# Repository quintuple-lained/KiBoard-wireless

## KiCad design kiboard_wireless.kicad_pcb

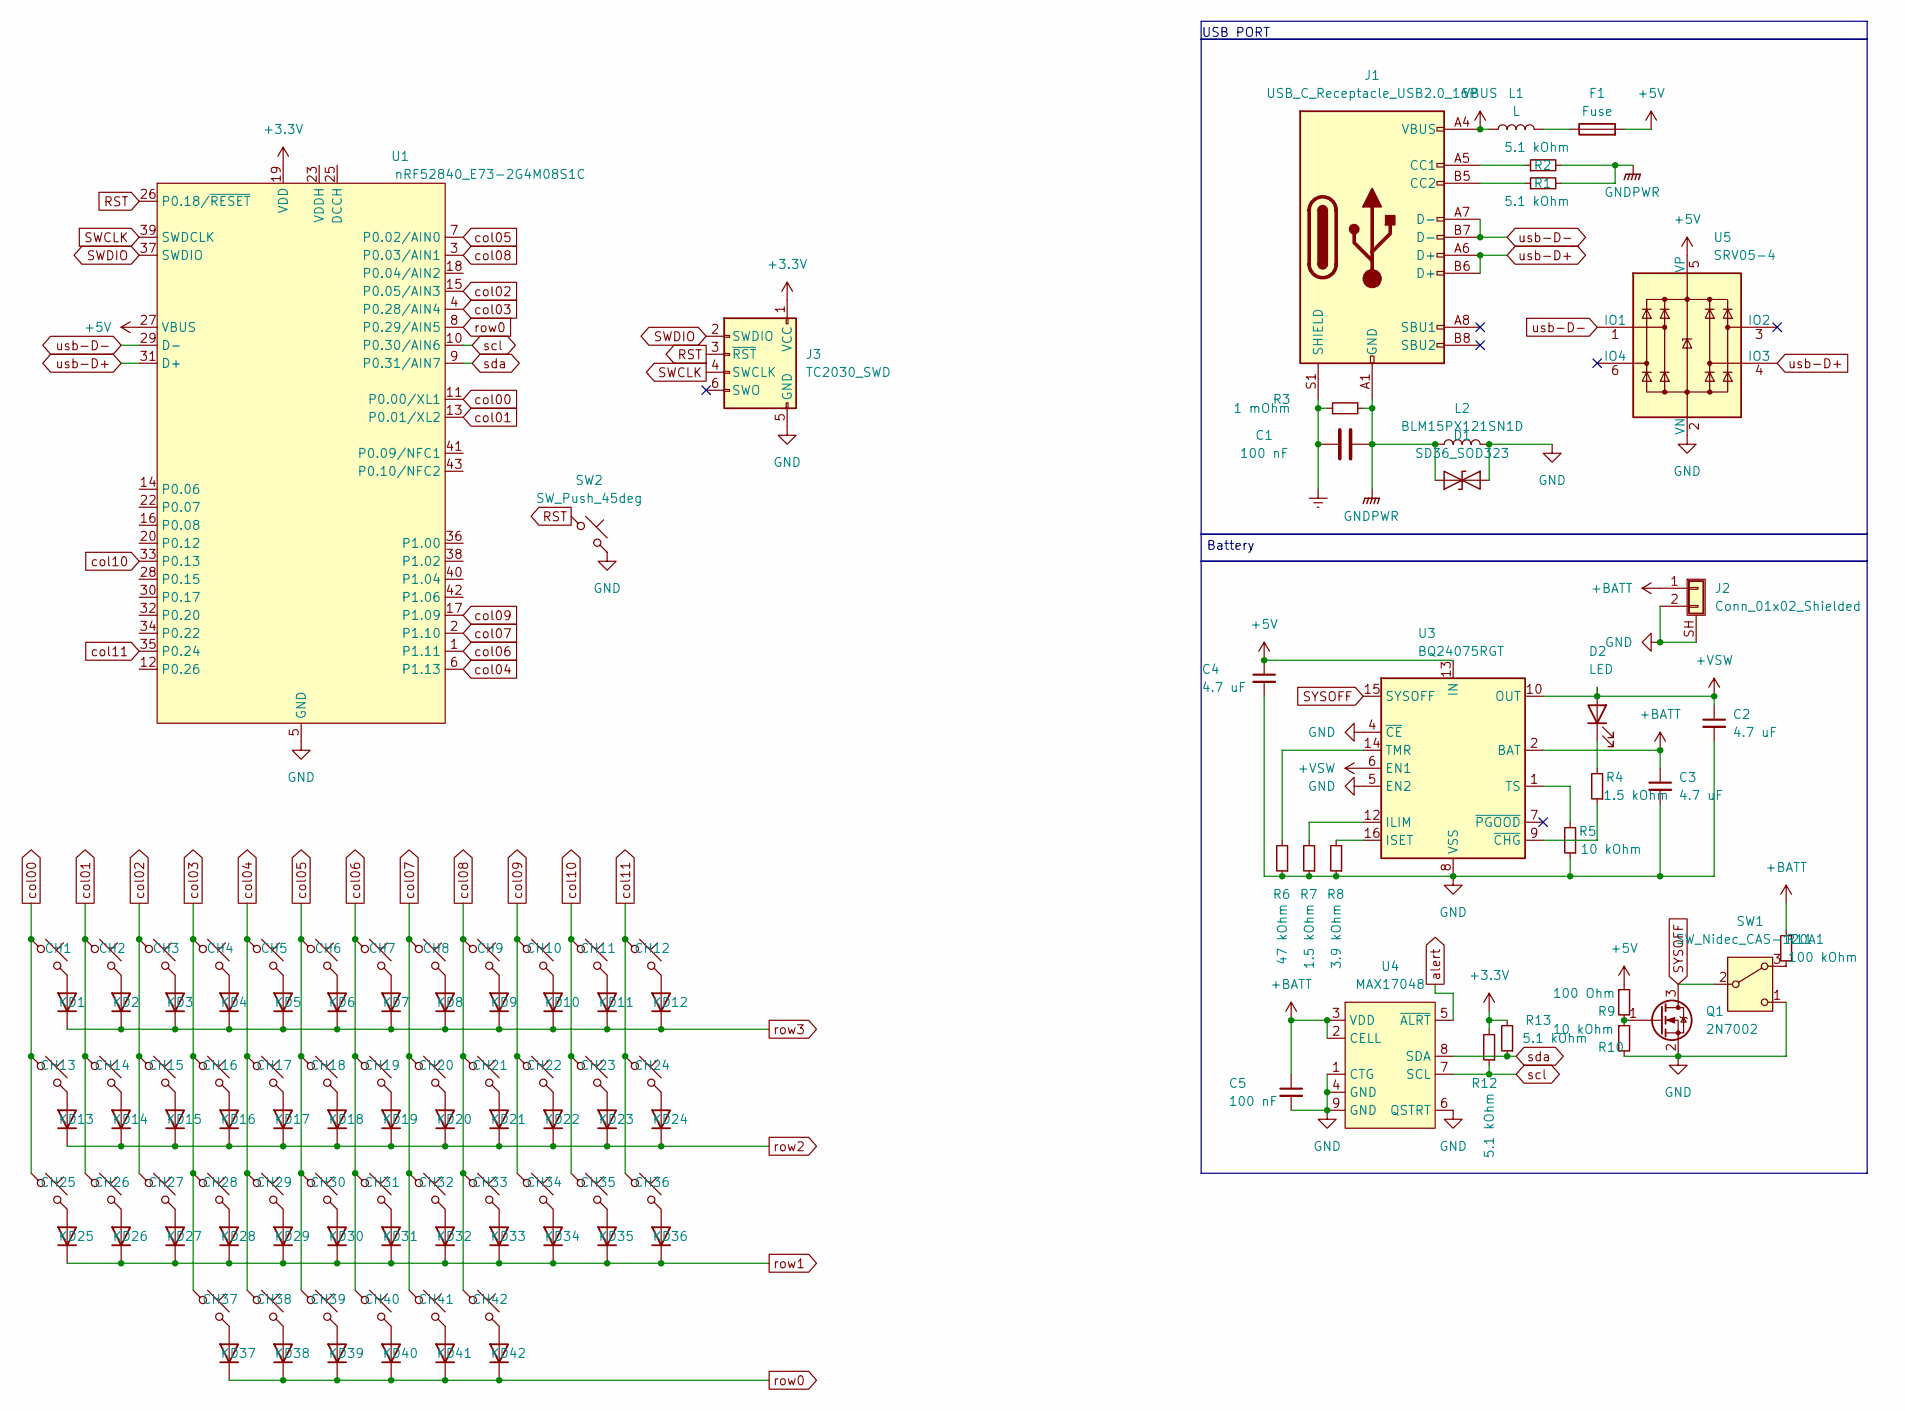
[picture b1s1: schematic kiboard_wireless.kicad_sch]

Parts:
C1, C5: 100 nF; C_1206_3216Metric
C2, C3, C4: 4.7 uF; C_1206_3216Metric
CH1, CH2, CH3, CH4, CH5, CH6, CH7, CH8, CH9, CH10, CH11, CH12, CH13, CH14, CH15, CH16, CH17, CH18, CH19, CH20, CH21, CH22, CH23, CH24, CH25, CH26, CH27, CH28, CH29, CH30, CH31, CH32, CH33, CH34, CH35, CH36, CH37, CH38, CH39, CH40, CH41, CH42: KS33_SW_HS; SW_KS33_HS_KS-2P02B01-02_HS_1u
D1: SD36_SOD323; D_SOD-323
D2: LED; LED_1206_3216Metric
F1: Fuse; Fuse_1206_3216Metric
J1: USB_C_Receptacle_USB2.0_16P; USB_C_Receptacle_HRO_TYPE-C-31-M-14
J2: Conn_01x02_Shielded; JST_PH_B2B-PH-SM4-TB_1x02-1MP_P2.00mm_Vertical
J3: TC2030_SWD; CON_TC2030_outlined
KD1, KD2, KD3, KD4, KD5, KD6, KD7, KD8, KD9, KD10, KD11, KD12, KD13, KD14, KD15, KD16, KD17, KD18, KD19, KD20, KD21, KD22, KD23, KD24, KD25, KD26, KD27, KD28, KD29, KD30, KD31, KD32, KD33, KD34, KD35, KD36, KD37, KD38, KD39, KD40, KD41, KD42: 1N4448W; D_SOD-123
L1: L; L_1206_3216Metric_Pad1.42x1.75mm_HandSolder
L2: BLM15PX121SN1D; L_1206_3216Metric
Q1: 2N7002; SOT-23
R1, R2, R12, R13: 5.1 kOhm; R_1206_3216Metric
R3: 1 mOhm; R_1206_3216Metric
R4, R7: 1.5 kOhm; R_1206_3216Metric
R5, R10: 10 kOhm; R_1206_3216Metric
R6: 47 kOhm; R_1206_3216Metric
R8: 3.9 kOhm; R_1206_3216Metric
R9: 100 Ohm; R_1206_3216Metric
R11: 100 kOhm; R_1206_3216Metric
SW1: SW_Nidec_CAS-120A1; SW_MSK12C02-HB
SW2: SW_Push_45deg; SW_SPST_SKQG_WithStem
U1: nRF52840_E73-2G4M08S1C; LCSC C356849
U3: BQ24075RGT; VQFN-16-1EP_3x3mm_P0.5mm_EP1.6x1.6mm
U4: MAX17048; DFN-8-1EP_2x2mm_P0.5mm_EP0.7x1.3mm
U5: SRV05-4; SOT-23-6-routable

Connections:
+3.3V: J3.1 (VCC), R12.2, R13.2, U1.19 (VDD)
+5V: C4.1, F1.2, R9.1, U1.27 (VBUS), U3.13 (IN), U5.5 (VP)
+BATT: C3.1, C5.1, J2.1, R11.2, U3.2 (BAT), U3.3 (BAT), U4.2 (CELL), U4.3 (VDD)
+VSW: C2.1, D2.2 (A), U3.6 (EN1), U3.10 (OUT), U3.11 (OUT)
Earth: C1.1, J1.S1 (SHIELD), R3.1
GND: C2.2, C3.2, C4.2, C5.2, D1.2 (A2), J2.2, J2.SH (Shield), J3.5 (GND), L2.2, Q1.2 (S), R5.1, R6.1, R7.1, R8.1, R10.2, SW1.1 (C), SW2.2, U1.5 (GND), U1.21 (GND), U1.24 (GND), U3.4 (~CE), U3.5 (EN2), U3.8 (VSS), U3.17 (VSS), U4.1 (CTG), U4.4 (GND), U4.6 (QSTRT), U4.9 (GND), U5.2 (VN)
GNDPWR: C1.2, D1.1 (A1), J1.A1 (GND), J1.A12 (GND), J1.B1 (GND), J1.B12 (GND), L2.1, R1.2, R2.2, R3.2
unnamed: D2.1 (K), R4.2
unnamed: F1.1, L1.2
unnamed: J1.A5 (CC1), R2.1
unnamed: J1.B5 (CC2), R1.1
unnamed: CH1.2, KD1.2 (A)
unnamed: CH2.2, KD2.2 (A)
unnamed: CH3.2, KD3.2 (A)
unnamed: CH4.2, KD4.2 (A)
unnamed: CH5.2, KD5.2 (A)
unnamed: CH6.2, KD6.2 (A)
unnamed: CH7.2, KD7.2 (A)
unnamed: CH8.2, KD8.2 (A)
unnamed: CH9.2, KD9.2 (A)
unnamed: CH10.2, KD10.2 (A)
unnamed: CH11.2, KD11.2 (A)
unnamed: CH12.2, KD12.2 (A)
unnamed: CH13.2, KD13.2 (A)
unnamed: CH14.2, KD14.2 (A)
unnamed: CH15.2, KD15.2 (A)
unnamed: CH16.2, KD16.2 (A)
unnamed: CH17.2, KD17.2 (A)
unnamed: CH18.2, KD18.2 (A)
unnamed: CH19.2, KD19.2 (A)
unnamed: CH20.2, KD20.2 (A)
unnamed: CH21.2, KD21.2 (A)
unnamed: CH22.2, KD22.2 (A)
unnamed: CH23.2, KD23.2 (A)
unnamed: CH24.2, KD24.2 (A)
unnamed: CH25.2, KD25.2 (A)
unnamed: CH26.2, KD26.2 (A)
unnamed: CH27.2, KD27.2 (A)
unnamed: CH28.2, KD28.2 (A)
unnamed: CH29.2, KD29.2 (A)
unnamed: CH30.2, KD30.2 (A)
unnamed: CH31.2, KD31.2 (A)
unnamed: CH32.2, KD32.2 (A)
unnamed: CH33.2, KD33.2 (A)
unnamed: CH34.2, KD34.2 (A)
unnamed: CH35.2, KD35.2 (A)
unnamed: CH36.2, KD36.2 (A)
unnamed: CH37.2, KD37.2 (A)
unnamed: CH38.2, KD38.2 (A)
unnamed: CH39.2, KD39.2 (A)
unnamed: CH40.2, KD40.2 (A)
unnamed: CH41.2, KD41.2 (A)
unnamed: CH42.2, KD42.2 (A)
unnamed: Q1.1 (G), R9.2, R10.1
unnamed: R11.1, SW1.3 (A)
unnamed: R7.2, U3.12 (ILIM)
unnamed: R8.2, U3.16 (ISET)
unnamed: R6.2, U3.14 (TMR)
unnamed: R5.2, U3.1 (TS)
unnamed: R4.1, U3.9 (~CHG)
RST: J3.3 (~RST), SW2.1, U1.26 (P0.18/~RESET)
SWCLK: J3.4 (SWCLK), U1.39 (SWDCLK)
SWDIO: J3.2 (SWDIO), U1.37 (SWDIO)
SYSOFF: Q1.3 (D), SW1.2 (B), U3.15 (SYSOFF)
VBUS: J1.A4 (VBUS), J1.A9 (VBUS), J1.B4 (VBUS), J1.B9 (VBUS), L1.1
alert: U4.5 (~ALRT)
col00: CH1.1, CH13.1, CH25.1, U1.11 (P0.00/XL1)
col01: CH2.1, CH14.1, CH26.1, U1.13 (P0.01/XL2)
col02: CH3.1, CH15.1, CH27.1, U1.15 (P0.05/AIN3)
col03: CH4.1, CH16.1, CH28.1, CH37.1, U1.4 (P0.28/AIN4)
col04: CH5.1, CH17.1, CH29.1, CH38.1, U1.6 (P1.13)
col05: CH6.1, CH18.1, CH30.1, CH39.1, U1.7 (P0.02/AIN0)
col06: CH7.1, CH19.1, CH31.1, CH40.1, U1.1 (P1.11)
col07: CH8.1, CH20.1, CH32.1, CH41.1, U1.2 (P1.10)
col08: CH9.1, CH21.1, CH33.1, CH42.1, U1.3 (P0.03/AIN1)
col09: CH10.1, CH22.1, CH34.1, U1.17 (P1.09)
col10: CH11.1, CH23.1, CH35.1, U1.33 (P0.13)
col11: CH12.1, CH24.1, CH36.1, U1.35 (P0.24)
row0: KD37.1 (K), KD38.1 (K), KD39.1 (K), KD40.1 (K), KD41.1 (K), KD42.1 (K), U1.8 (P0.29/AIN5)
row1: KD25.1 (K), KD26.1 (K), KD27.1 (K), KD28.1 (K), KD29.1 (K), KD30.1 (K), KD31.1 (K), KD32.1 (K), KD33.1 (K), KD34.1 (K), KD35.1 (K), KD36.1 (K)
row2: KD13.1 (K), KD14.1 (K), KD15.1 (K), KD16.1 (K), KD17.1 (K), KD18.1 (K), KD19.1 (K), KD20.1 (K), KD21.1 (K), KD22.1 (K), KD23.1 (K), KD24.1 (K)
row3: KD1.1 (K), KD2.1 (K), KD3.1 (K), KD4.1 (K), KD5.1 (K), KD6.1 (K), KD7.1 (K), KD8.1 (K), KD9.1 (K), KD10.1 (K), KD11.1 (K), KD12.1 (K)
scl: R12.1, U1.10 (P0.30/AIN6), U4.7 (SCL)
sda: R13.1, U1.9 (P0.31/AIN7), U4.8 (SDA)
usb-D+: J1.A6 (D+), J1.B6 (D+), U1.31 (D+), U5.4 (IO3)
usb-D-: J1.A7 (D-), J1.B7 (D-), U1.29 (D-), U5.1 (IO1)

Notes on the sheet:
Battery
USB PORT

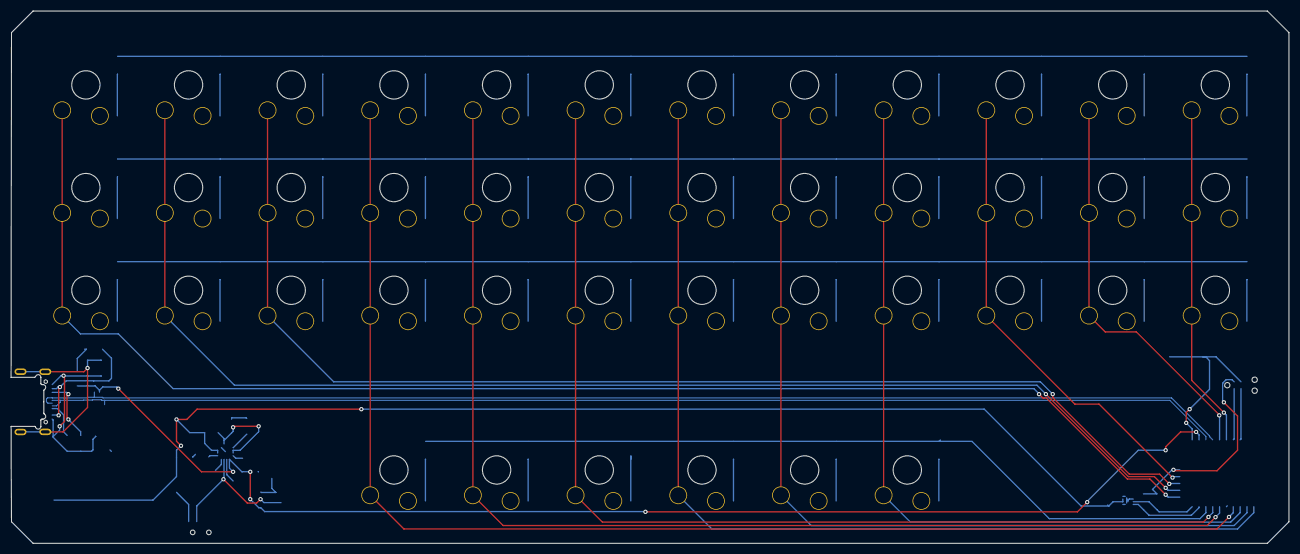
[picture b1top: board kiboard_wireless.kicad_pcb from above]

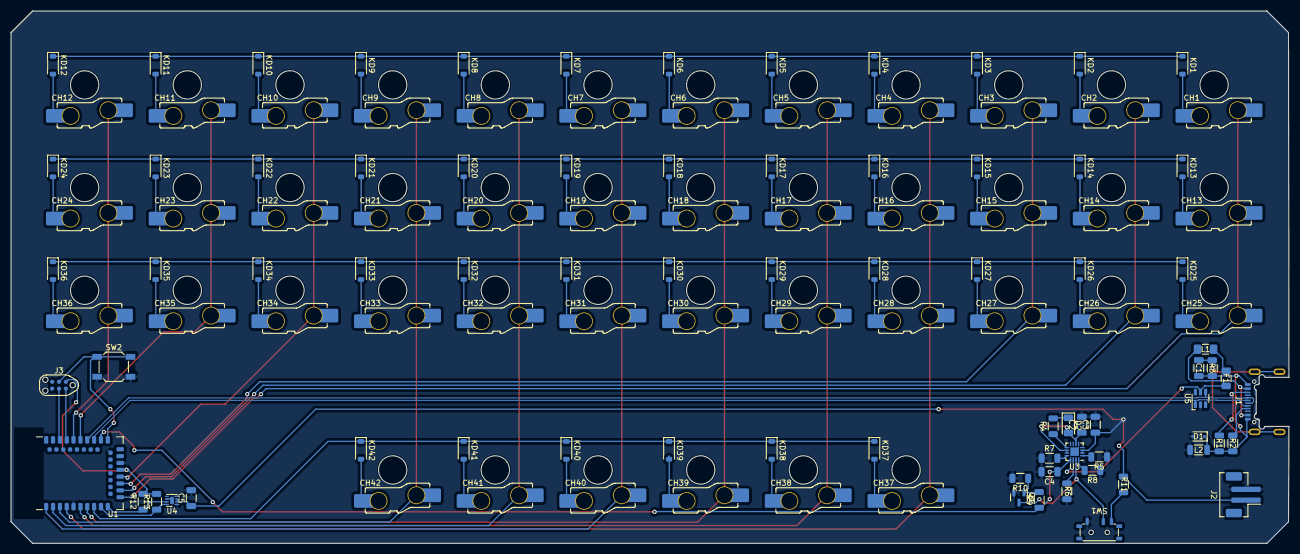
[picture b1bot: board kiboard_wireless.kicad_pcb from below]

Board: 2 copper layers, 237.1 x 98.8 mm, 117 parts (117 on the bottom side), 85 nets.

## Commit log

2024-02-21 added files
2024-02-21 keymatrix done
2024-02-21 fixed weird trace
2024-02-21 pain
2024-02-22 done
2024-02-22 improvements
2024-02-22 git gnore? *
2024-02-22 git gnore!
2024-02-22 increased size of the scheet
2024-02-22 bump
2024-02-22 fucking finally
2024-02-22 done for now
2024-02-23 cosmetic improvements
